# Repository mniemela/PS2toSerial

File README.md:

# PS2toSerial
PS/2 to serial converter using ATtiny4313 and MAX232. There are plenty of similar projects, but almost all of them are external, so here's my internal version
which draws power from floppy power connector.

## Description

This does essentially the same thing as other PS/2 to serial adapters: it interfaces with PS/2 mouse, and pretends to be a serial mouse to the computer.

It has following features:
* Support for normal 1200 baud serial, or 9600 baud high speed mode
* Support for wheel mouse
* Sample rate is selected from 20/40/60/100/200 with jumpers. For higher than 40, 9600 baud serial is needed.
* Resolution is configured with jumpers
* Option for USB A connector, so no need for a passive USB->PS/2 -adapter
* Option for PS/2 connector is also provided
* Supports hotplugging
* Crystal oscillator for ensuring accurate baud rate
* TVS diodes for ESD protection
* Overcurrent protection using ATtiny4313's onboard analog comparator and a P-type MOSFET as a switch
* No SMD components, so it's easy to assemble
* Programming via SPI header
* Supports combining movement packets in 1200 baud mode as a KVM workaround

Jumpers J1 sets baud rate, closed is high speed mode. J2 and J3 sets sample rate as described in silkscreen, and J4 and J4 set resolution.

Using 9600 baud serial speed requires modified mouse drivers, which can be found for example from this project:
https://github.com/LimeProgramming/USB-serial-mouse-adapter/tree/main

There are footprints for both USB-A and mini-DIN6 or PS/2 connector, only one of them should be populated.

## KVM issues

Some KVM switches ignore commands to set sample rate. The adapter tries to set baud rate to configured value, but the KVM will ignore 
it and packets are received faster than they can be sent to PC. As a new feature, this adapter combines data in movement packets
so that they don't have to be dropped.

Also, some KVM switches randomly reset in middle of normal operation. There's a workaround for this as well.

## Technical details

ATtiny has both hardware USART and Universal Serial Interface or USI, which is readily adaptable to PS/2, so there's only minimal need for bit banging. USI provides 
start condition detector with interrupt and counter (increased at PS/2's clock rising and falling edge) overflow interrupt, which removes need for polling. Instead
of sampling data on falling clock edge, this adapter uses rising edge as all the devices I have measured change data line state closer to falling than rising edge.
In particular, with a KVM switch this was within as little as 3µs from falling edge!

Resistors R8 and R9 form voltage divider for analog comparator positive input pin. R7 is used as a shunt resistor for current detection, voltage after it goes to
comparator's negative input pin. Comparator's output is monitored by interrupt from timer 0 every 100µs, and if there's overcurrent for 1ms, power to PS/2 is shut down.

RTS and DTR signals to pins PB2 and PB3 are monitored with pin change interrupt. When either of them goes down and then back up, mouse detection characters are sent if
mouse is connected.

Normally PS/2 host doesn't know whether mouse is disconnected or is just still, so the adapter polls mouse by sending command enable data reporting or 0xF4 every two
seconds. If mouse is connected, it replys with an ACK or 0xFA, if it's disconnected, there's no clock signal which is detected.

Some KVM switches randomly reset in the middle of normal operation and send 0xAA and 0x00 as during boot, then stopping to send movement data. This adapter attempts
to detect this situation and recover from it.

\
**BOM of specific components:**
| Ref. | Part. no. | Note |
|---|---|---|
| Q1 | MTD20P06HDL | Any DPAK logic level P-channel enhancement-type MOSFET with similar pinout will work. |
| U1 | ATtiny4313-PU | Microcontroller |
| U2 | MAX232 | RS-232 transceiver |
| R7 | 560mΩ resistor | Anything with max. dissipation > 600mW will work. |
| Y1 | AS-18.432-20 | Other frequencies up to 20M can be used, but will require modifications to software. |
| D2-D4 | P6KE6.8 | TVS diode with 5.8V working voltage |
| J10 | MDC-206 | mini-DIN6 connector |
| J12, J13 | AMT0440051DB0000G | M4 screw terminal |
| C6 | ??? | Exact value of this capacitor isn't important. |

## Building software and MCU fuse settings

This has been built with Microchip studio, currently there's no Makefile for other toolchains. When programming the MCU, fuses must also be set. Correct setting for
high fuse is 0xDF and for low fuse 0xFF.

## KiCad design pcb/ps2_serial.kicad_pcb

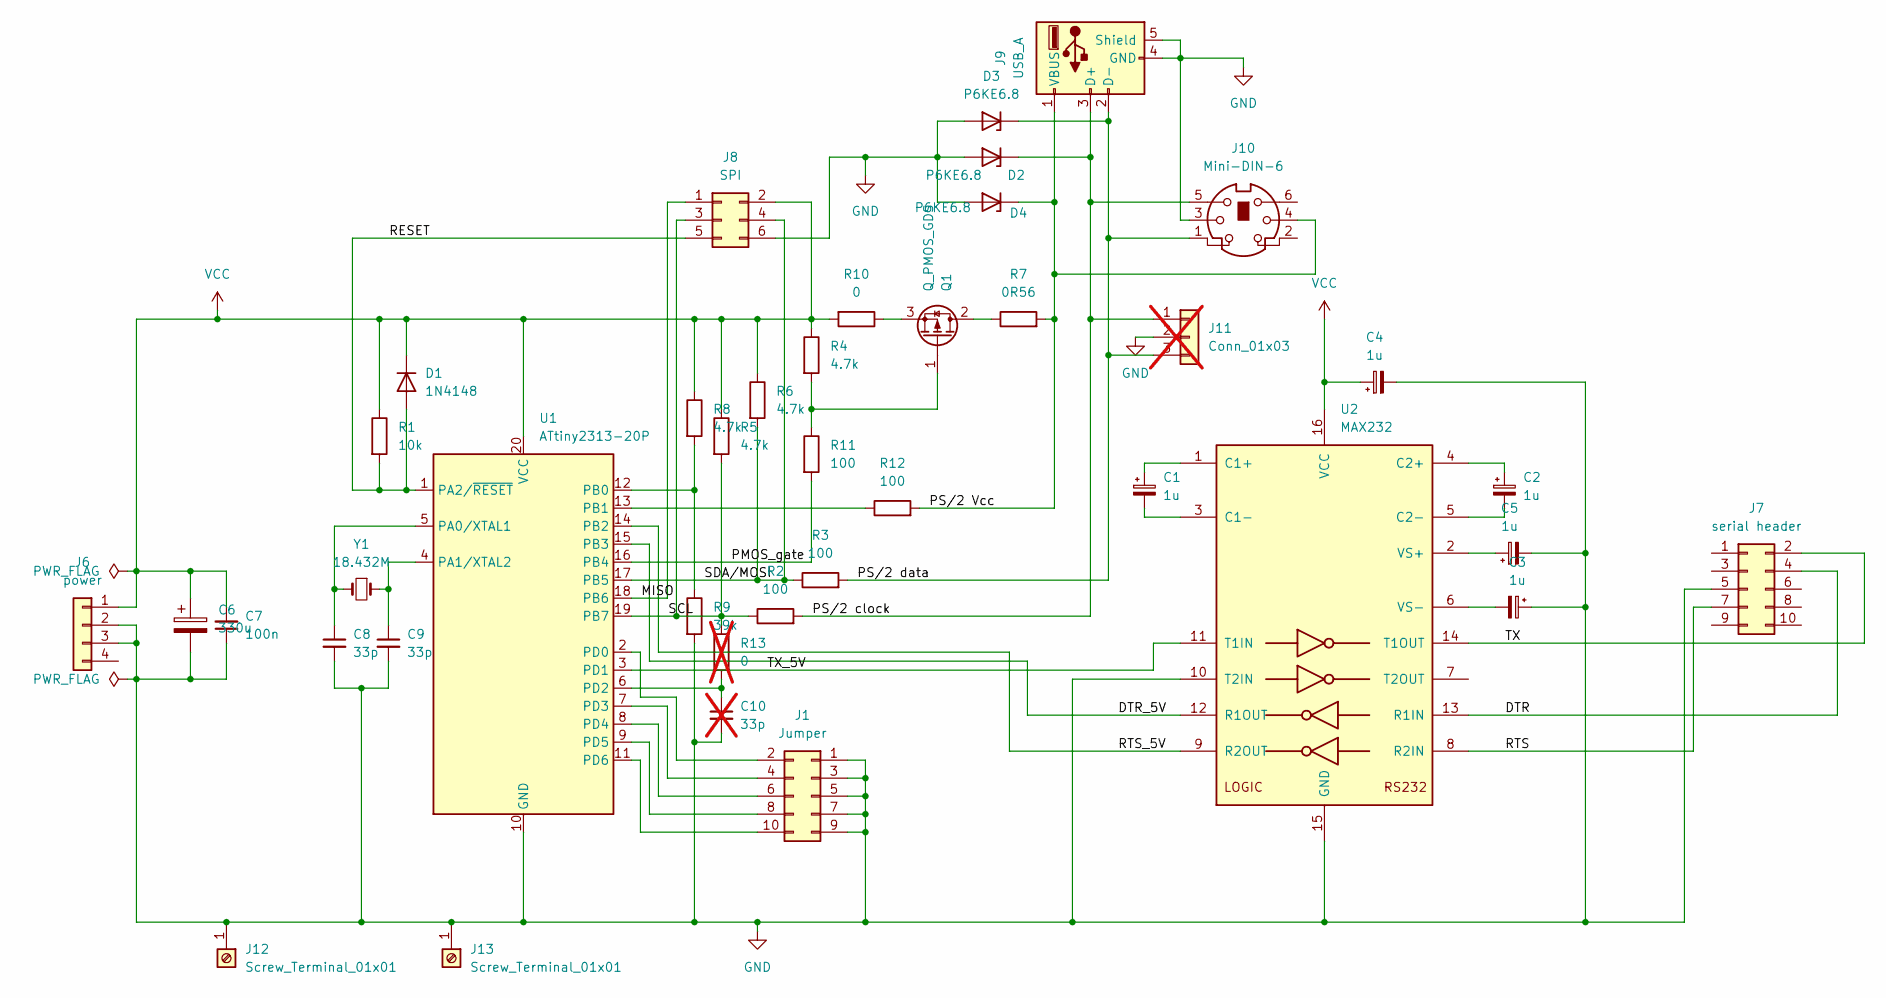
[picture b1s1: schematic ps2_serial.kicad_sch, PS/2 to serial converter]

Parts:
C1, C2, C3, C4, C5: 1u; CP_Radial_D5.0mm_P2.50mm
C6: 330u; CP_Radial_D8.0mm_P3.50mm
C7: 100n; C_Rect_L7.0mm_W2.5mm_P5.00mm
C8, C9: 33p; C_Disc_D4.3mm_W1.9mm_P5.00mm
C10: 33p; C_Disc_D4.3mm_W1.9mm_P5.00mm; not fitted
D1: 1N4148; D_DO-35_SOD27_P7.62mm_Horizontal
D2, D3, D4: P6KE6.8; D_DO-15_P10.16mm_Horizontal
J1: Jumper; PinHeader_2x05_P2.54mm_Vertical
J6: power; Molex_Nano-Fit_105313-xx04_1x04_P2.50mm_Horizontal
J7: serial header; PinHeader_2x05_P2.54mm_Vertical
J8: SPI; PinHeader_2x03_P2.54mm_Vertical
J9: USB_A; USB_A_Molex_67643_Horizontal
J10: Mini-DIN-6; J_Mini-DIN-6
J11: Conn_01x03; PinHeader_1x03_P2.54mm_Vertical; not fitted
J12, J13: Screw_Terminal_01x01; Amphenol_M4-44051DB
Q1: Q_PMOS_GDS; TO-252-2
R1: 10k; R_Axial_DIN0207_L6.3mm_D2.5mm_P10.16mm_Horizontal
R2, R3, R11, R12: 100; R_Axial_DIN0207_L6.3mm_D2.5mm_P10.16mm_Horizontal
R4, R5, R6, R8: 4.7k; R_Axial_DIN0207_L6.3mm_D2.5mm_P10.16mm_Horizontal
R7: 0R56; R_Axial_DIN0411_L9.9mm_D3.6mm_P12.70mm_Horizontal
R9: 39k; R_Axial_DIN0207_L6.3mm_D2.5mm_P10.16mm_Horizontal
R10: 0; R_Axial_DIN0207_L6.3mm_D2.5mm_P10.16mm_Horizontal
R13: 0; R_Axial_DIN0207_L6.3mm_D2.5mm_P10.16mm_Horizontal; not fitted
U1: ATtiny2313-20P; DIP-20_W7.62mm_Socket_LongPads
U2: MAX232; DIP-16_W7.62mm_LongPads
Y1: 18.432M; Crystal_HC49-U_Vertical

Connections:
/DTR: J7.4, U2.13 (R1IN)
/DTR_5V: U1.15 (PB3), U2.12 (R1OUT)
/MISO: J8.1, U1.18 (PB6)
/PMOS_gate: R11.2, U1.16 (PB4)
/PS/2 Vcc: D4.1 (K), J9.1 (VBUS), J10.4, R7.2, R12.2
/PS/2 clock: D2.1 (K), J9.3 (D+), J10.5, J11.1, R2.2
/PS/2 data: D3.1 (K), J9.2 (D-), J10.1, J11.3, R3.2
/RESET: D1.2 (A), J8.5, R1.2, U1.1 (PA2/~RESET)
/RTS: J7.7, U2.8 (R2IN)
/RTS_5V: U1.14 (PB2), U2.9 (R2OUT)
/SCL: J8.3, R2.1, R5.2, R13.1, U1.19 (PB7)
/SDA/MOSI: J8.4, R3.1, R6.2, U1.17 (PB5)
/TX: J7.2, U2.14 (T1OUT)
/TX_5V: U1.3 (PD1), U2.11 (T1IN)
GND: C3.1, C4.2, C5.2, C6.2, C7.1, C8.2, C9.2, C10.2, D2.2 (A), D3.2 (A), D4.2 (A), J1.1, J1.3, J1.5, J1.7, J1.9, J6.2, J6.3, J7.5, J8.6, J9.4 (GND), J9.5 (Shield), J10.3, J10.C1, J10.C2, J10.SH, J11.2, J12.1, J13.1, R9.2, U1.10 (GND), U2.10 (T2IN), U2.15 (GND)
unnamed: J1.2, U1.2 (PD0)
unnamed: J1.4, U1.7 (PD3)
unnamed: J1.6, U1.8 (PD4)
unnamed: J1.8, U1.9 (PD5)
unnamed: J1.10, U1.11 (PD6)
unnamed: Q1.2 (D), R7.1
unnamed: Q1.1 (G), R4.2, R11.1
unnamed: Q1.3 (S), R10.1
unnamed: C8.1, U1.5 (PA0/XTAL1), Y1.2
unnamed: C9.1, U1.4 (PA1/XTAL2), Y1.1
unnamed: R8.2, R9.1, U1.12 (PB0)
unnamed: R12.1, U1.13 (PB1)
unnamed: C10.1, R13.2, U1.6 (PD2)
unnamed: C1.1, U2.1 (C1+)
unnamed: C1.2, U2.3 (C1-)
unnamed: C2.1, U2.4 (C2+)
unnamed: C2.2, U2.5 (C2-)
unnamed: C5.1, U2.2 (VS+)
unnamed: C3.2, U2.6 (VS-)
VCC: C4.1, C6.1, C7.2, D1.1 (K), J6.1, J8.2, R1.1, R4.1, R5.1, R6.1, R8.1, R10.2, U1.20 (VCC), U2.16 (VCC)

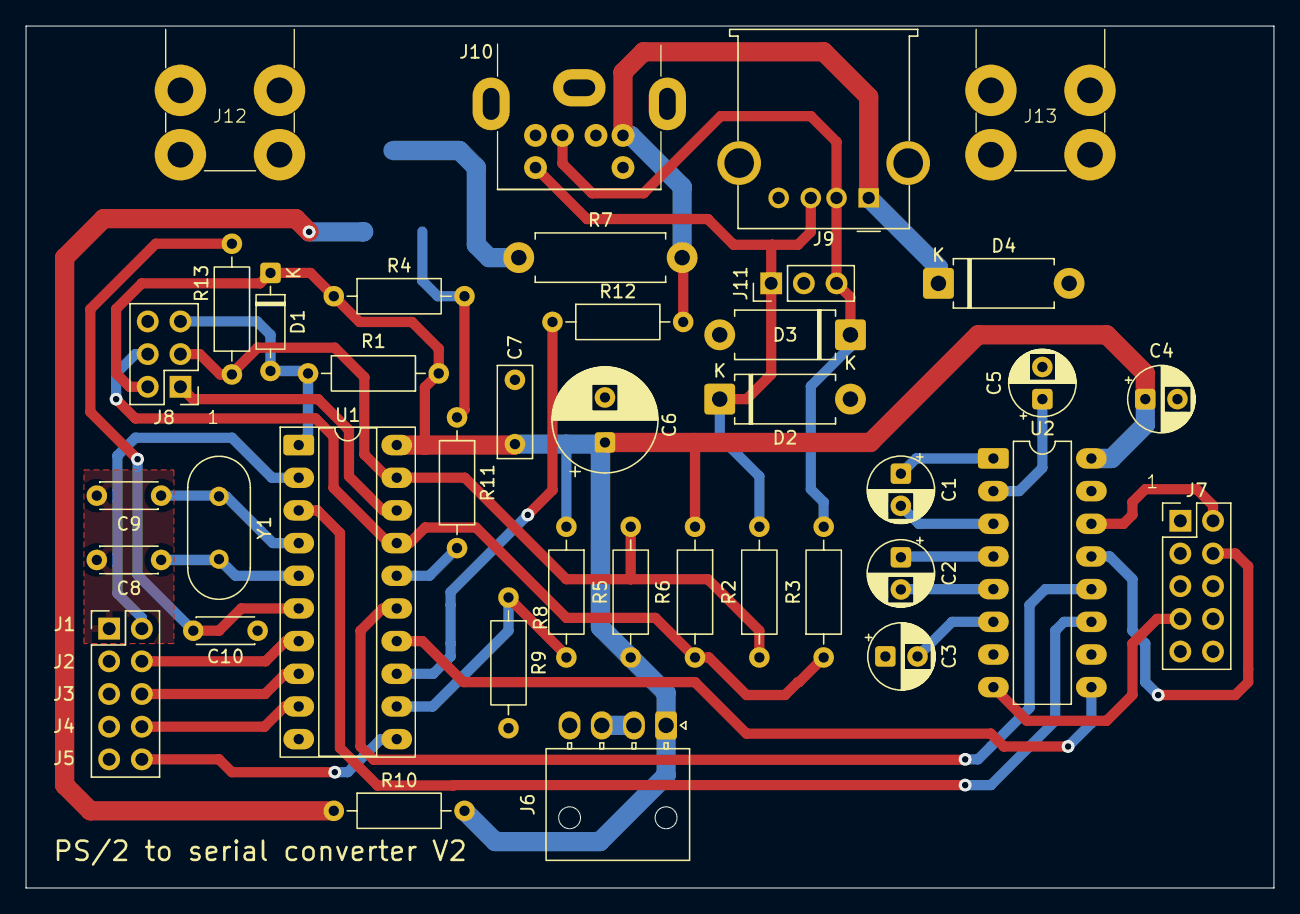
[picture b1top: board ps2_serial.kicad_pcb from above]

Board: 2 copper layers, 97.0 x 67.0 mm, 40 parts (1 on the bottom side), 35 nets.

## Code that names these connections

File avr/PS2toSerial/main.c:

/*
 * PS2toSerial.c
 *
 * Created: 3.1.2026 8.05.48
 * Author : Mikael Niemelä
 */

#include <avr/io.h>
#include <avr/interrupt.h>
#include <inttypes.h>

#include "constants.h"
#include "ps2.h"
#include "uart.h"
#include <util/delay.h>

void init() {
	
	//turn on pullups for jumpers and unused pins
	PORTD = ~(1<<PD1);
	PORTB = 1 << PB6;
	
	//turn off comparator digital inputs
	DIDR = (1<<AIN1D) | (1<<AIN0D);
	
	_delay_us(100);
	
	// check jumpers for sample rate and baud rate
	uint8_t sampleRate = 0;
	uint8_t highSpeedUart = !((1 << PIND0) & PIND);
	if (highSpeedUart) {
		if (((1 << PIND3) & PIND) && ((1 << PIND4) & PIND) )
			sampleRate = 40;
		else if ((1 << PIND3) & PIND)
			sampleRate = 60;
		else if ((1 << PIND4) & PIND)
			sampleRate = 100;
		else
			sampleRate = 200;
	} else {
		if ((1 << PIND4) & PIND)
			sampleRate = 40;
		else
			sampleRate = 20;
	}
	
	//check jumpers for resolution
	uint8_t resolution = (((1 << PIND5) | (1 << PIND6)) & PIND) >> 5;
	
	
	uart_init(highSpeedUart);
	ps2_init(sampleRate, resolution, highSpeedUart);
	
	//turn on device power
	DDRB = 1<<PB4;
	
	//init timer0 for interrupt every 100µs
	OCR0A = (uint8_t)((F_CPU) * 0.0001 / 8 + 0.5);
	TCCR0A = (1 << COM0A1) | (1 << WGM01);
	TCCR0B = 1 << CS01;
	TIMSK |= (1 << OCIE0A);
	
	//init pin change interrupt for detecting RTS or DTR low
	PCMSK = (1<<PCINT2) | (1<<PCINT3);
	GIMSK = 1<<PCIE0;

	sei();
}

int main(void)
{
    init();
	
    while (1) 
    {
    }
}

ISR(PCINT0_vect) {
	//send detection characters when RTS or DTR goes back up
	static uint8_t previousState = 0;
	uint8_t currentState = PINB & ((1<<PB2) | (1<<PB3));
	uint8_t dtrValue = currentState & (1<<PB3);
	uint8_t rtsValue = currentState & (1<<PB2);
	if ((!dtrValue && (previousState & (1<<PB3))) || (!rtsValue && (previousState & (1<<PB2)))) {
		char mouseType = getMouseType();
		if (mouseType) {
			addTxData('M');
			addTxData(mouseType);
			//send fake PnP package, looks like this is required by MS wheel mouse driver
			addTxData(0x08);
			addTxData(0x09);
			startTx();
		}
	}
	if (currentState != previousState)
		previousState = currentState;
}

ISR(TIMER0_COMPA_vect) {
	//don't do anything if power is already off
	if (PORTB & (1<<PB4))
		return;
	
	// increase counter when comparator output is on, otherwise decrement (until 0)
	static uint8_t counter = 0;
	if (ACSR & (1 << ACO)) {
			counter++;
		} else {
		if (counter > 0)
			counter--;
	}
	
	// turn power off after 1ms of overcurrent
	if (counter > 10)
		PORTB = PORTB | (1<<PB4);
}

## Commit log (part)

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2026-02-23 First version.
2026-02-26 Fixed compatibility issues with KVM switch and improved documentation.
2026-03-05 Change to ATtiny4313, some minor improvements.
2026-05-26 Added workaround for KVM switches that reset in the middle of normal operation.
2026-05-30 V2 for PCB. Implemented following changes: -more elegant mounting mechanism -more jumper settings -footprint for both USB and PS/2 socket -reservation for using INT0 to trigger SDA sampling -smaller 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
2026-05-30 Implemented changes for handling jumpers in new PCB and changed clock macro.
2026-06-04 Updated documentation.
